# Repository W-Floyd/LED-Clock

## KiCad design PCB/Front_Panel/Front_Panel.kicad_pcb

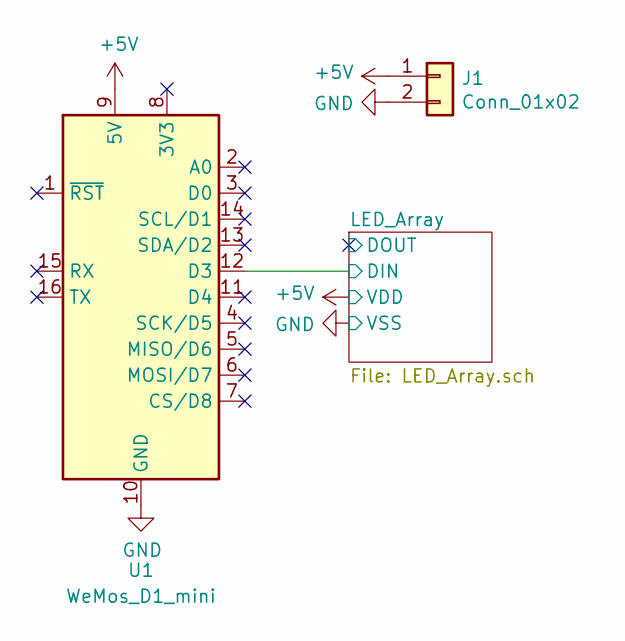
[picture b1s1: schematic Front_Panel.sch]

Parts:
J1: Conn_01x02; JST_XH_B2B-XH-AM_1x02_P2.50mm_Vertical
U1: WeMos_D1_mini; WEMOS_D1_mini_light

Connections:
+5V: J1.1, U1.9 (5V); also elsewhere on the board
/LED_Array/DIN: U1.12 (D3); also elsewhere on the board
GND: J1.2, U1.10 (GND); also elsewhere on the board

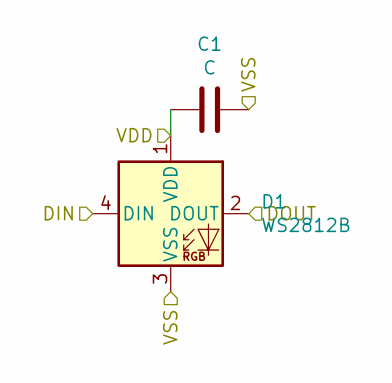
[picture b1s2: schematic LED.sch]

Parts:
C1: C; C_0402_1005Metric; LCSC Part C1525
D1: WS2812B; LED_WS2812B_PLCC4_5.0x5.0mm_P3.2mm; LCSC Part C114586

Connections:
+5V: C1.1, D1.1 (VDD); also elsewhere on the board
/LED_Array/Character/sheet607C81B4/DIN: D1.2 (DOUT); also elsewhere on the board
/LED_Array/DIN: D1.4 (DIN); also elsewhere on the board
GND: C1.2, D1.3 (VSS); also elsewhere on the board

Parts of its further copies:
C2, C3, C4, C5, C6, C7, C8, C9, C10, C11, C12, C13, C14, C15, C16, C17, C18, C19, C20, C21, C22, C23, C24, C25, C26, C27, C28: C; C_0402_1005Metric; LCSC Part C1525
D2, D3, D4, D5, D6, D7, D8, D9, D10, D11, D12, D13, D14, D15, D16, D17, D18, D19, D20, D21, D22, D23, D24, D25, D26, D27, D28: WS2812B; LED_WS2812B_PLCC4_5.0x5.0mm_P3.2mm; LCSC Part C114586

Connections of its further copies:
+5V: C2.1, C3.1, C4.1, C5.1, C6.1, C7.1, C8.1, C9.1, C10.1, C11.1, C12.1, C13.1, C14.1, C15.1, C16.1, C17.1, C18.1, C19.1, C20.1, C21.1, C22.1, C23.1, C24.1, C25.1, C26.1, C27.1, C28.1, D2.1 (VDD), D3.1 (VDD), D4.1 (VDD), D5.1 (VDD), D6.1 (VDD), D7.1 (VDD), D8.1 (VDD), D9.1 (VDD), D10.1 (VDD), D11.1 (VDD), D12.1 (VDD), D13.1 (VDD), D14.1 (VDD), D15.1 (VDD), D16.1 (VDD), D17.1 (VDD), D18.1 (VDD), D19.1 (VDD), D20.1 (VDD), D21.1 (VDD), D22.1 (VDD), D23.1 (VDD), D24.1 (VDD), D25.1 (VDD), D26.1 (VDD), D27.1 (VDD), D28.1 (VDD); also elsewhere on the board
/LED_Array/Character/sheet607C8FE9/DIN: D3.2 (DOUT), D4.4 (DIN)
/LED_Array/Character/sheet607C9E28/DIN: D5.2 (DOUT), D6.4 (DIN)
/LED_Array/Character/sheet607C81B4/DIN: D2.4 (DIN); also elsewhere on the board
/LED_Array/Character/sheet607C88E5/DIN: D2.2 (DOUT), D3.4 (DIN)
/LED_Array/Character/sheet607C96E8/DIN: D4.2 (DOUT), D5.4 (DIN)
/LED_Array/Character/sheet607CA522/DIN: D6.2 (DOUT), D7.4 (DIN)
/LED_Array/DOUT: D28.2 (DOUT)
/LED_Array/sheet607CAD2A/DIN: D7.2 (DOUT), D8.4 (DIN)
/LED_Array/sheet607CAD2A/sheet607C8FE9/DIN: D10.2 (DOUT), D11.4 (DIN)
/LED_Array/sheet607CAD2A/sheet607C9E28/DIN: D12.2 (DOUT), D13.4 (DIN)
/LED_Array/sheet607CAD2A/sheet607C81B4/DIN: D8.2 (DOUT), D9.4 (DIN)
/LED_Array/sheet607CAD2A/sheet607C88E5/DIN: D9.2 (DOUT), D10.4 (DIN)
/LED_Array/sheet607CAD2A/sheet607C96E8/DIN: D11.2 (DOUT), D12.4 (DIN)
/LED_Array/sheet607CAD2A/sheet607CA522/DIN: D13.2 (DOUT), D14.4 (DIN)
/LED_Array/sheet607CB27B/DIN: D14.2 (DOUT), D15.4 (DIN)
/LED_Array/sheet607CB27B/sheet607C8FE9/DIN: D17.2 (DOUT), D18.4 (DIN)
/LED_Array/sheet607CB27B/sheet607C9E28/DIN: D19.2 (DOUT), D20.4 (DIN)
/LED_Array/sheet607CB27B/sheet607C81B4/DIN: D15.2 (DOUT), D16.4 (DIN)
/LED_Array/sheet607CB27B/sheet607C88E5/DIN: D16.2 (DOUT), D17.4 (DIN)
/LED_Array/sheet607CB27B/sheet607C96E8/DIN: D18.2 (DOUT), D19.4 (DIN)
/LED_Array/sheet607CB27B/sheet607CA522/DIN: D20.2 (DOUT), D21.4 (DIN)
/LED_Array/sheet607CB803/DIN: D21.2 (DOUT), D22.4 (DIN)
/LED_Array/sheet607CB803/sheet607C8FE9/DIN: D24.2 (DOUT), D25.4 (DIN)
/LED_Array/sheet607CB803/sheet607C9E28/DIN: D26.2 (DOUT), D27.4 (DIN)
/LED_Array/sheet607CB803/sheet607C81B4/DIN: D22.2 (DOUT), D23.4 (DIN)
/LED_Array/sheet607CB803/sheet607C88E5/DIN: D23.2 (DOUT), D24.4 (DIN)
/LED_Array/sheet607CB803/sheet607C96E8/DIN: D25.2 (DOUT), D26.4 (DIN)
/LED_Array/sheet607CB803/sheet607CA522/DIN: D27.2 (DOUT), D28.4 (DIN)
GND: C2.2, C3.2, C4.2, C5.2, C6.2, C7.2, C8.2, C9.2, C10.2, C11.2, C12.2, C13.2, C14.2, C15.2, C16.2, C17.2, C18.2, C19.2, C20.2, C21.2, C22.2, C23.2, C24.2, C25.2, C26.2, C27.2, C28.2, D2.3 (VSS), D3.3 (VSS), D4.3 (VSS), D5.3 (VSS), D6.3 (VSS), D7.3 (VSS), D8.3 (VSS), D9.3 (VSS), D10.3 (VSS), D11.3 (VSS), D12.3 (VSS), D13.3 (VSS), D14.3 (VSS), D15.3 (VSS), D16.3 (VSS), D17.3 (VSS), D18.3 (VSS), D19.3 (VSS), D20.3 (VSS), D21.3 (VSS), D22.3 (VSS), D23.3 (VSS), D24.3 (VSS), D25.3 (VSS), D26.3 (VSS), D27.3 (VSS), D28.3 (VSS); also elsewhere on the board

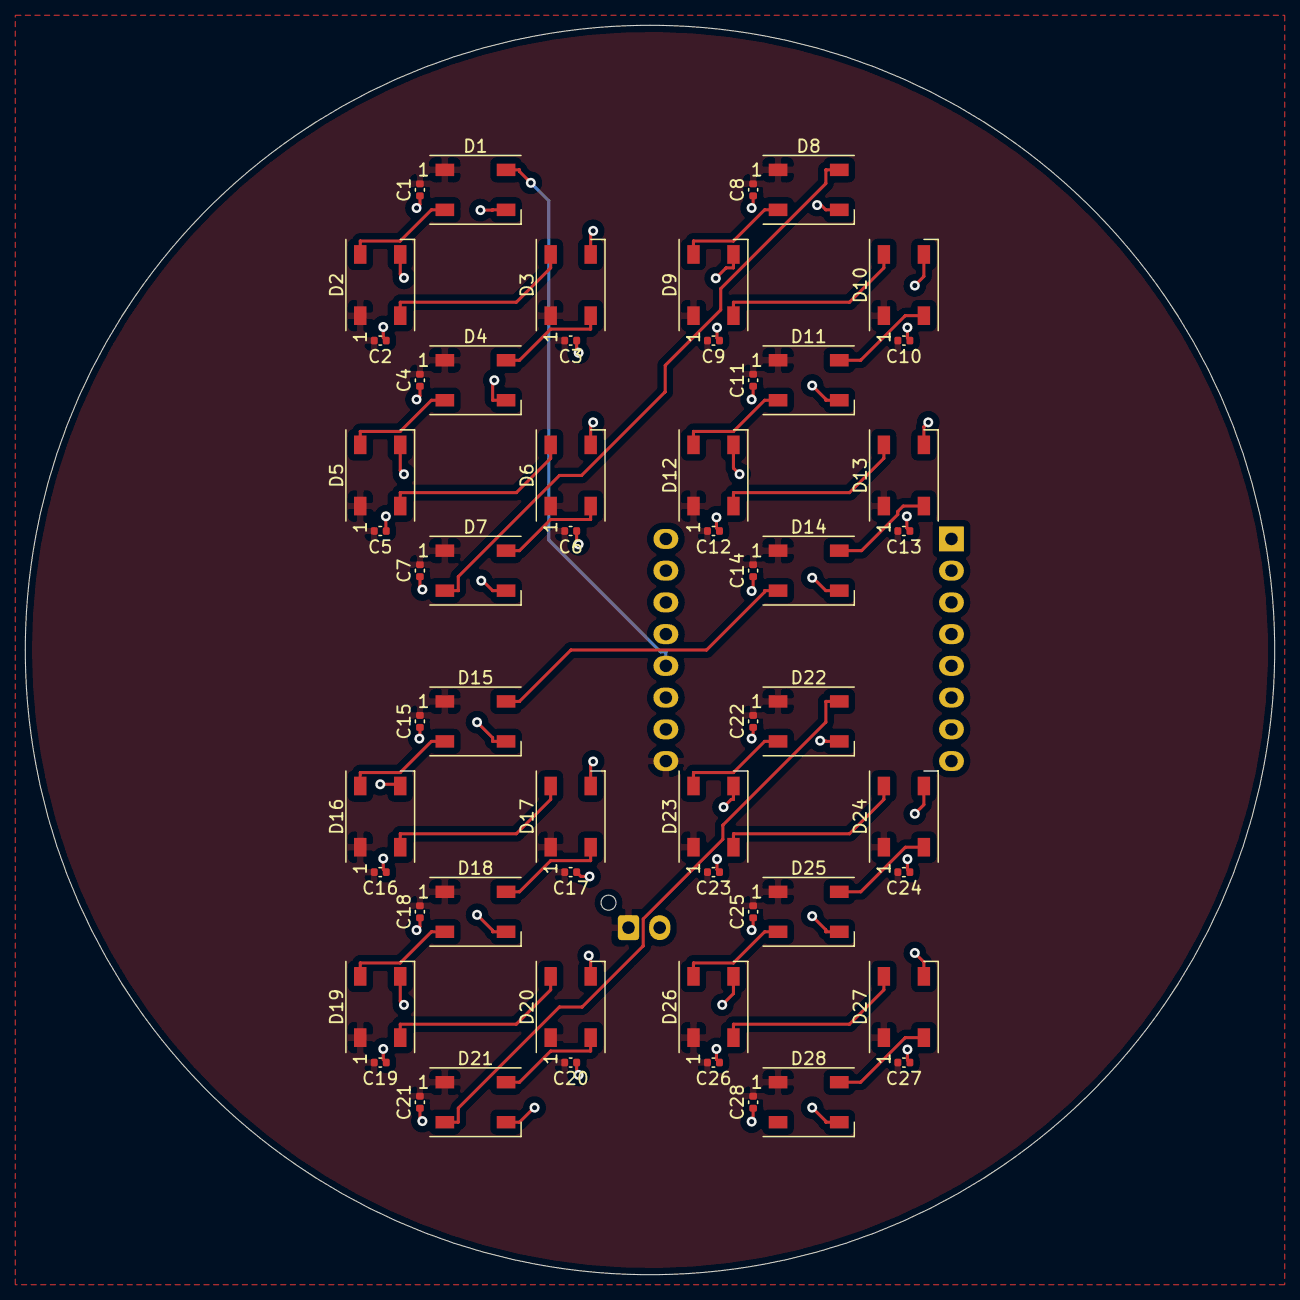
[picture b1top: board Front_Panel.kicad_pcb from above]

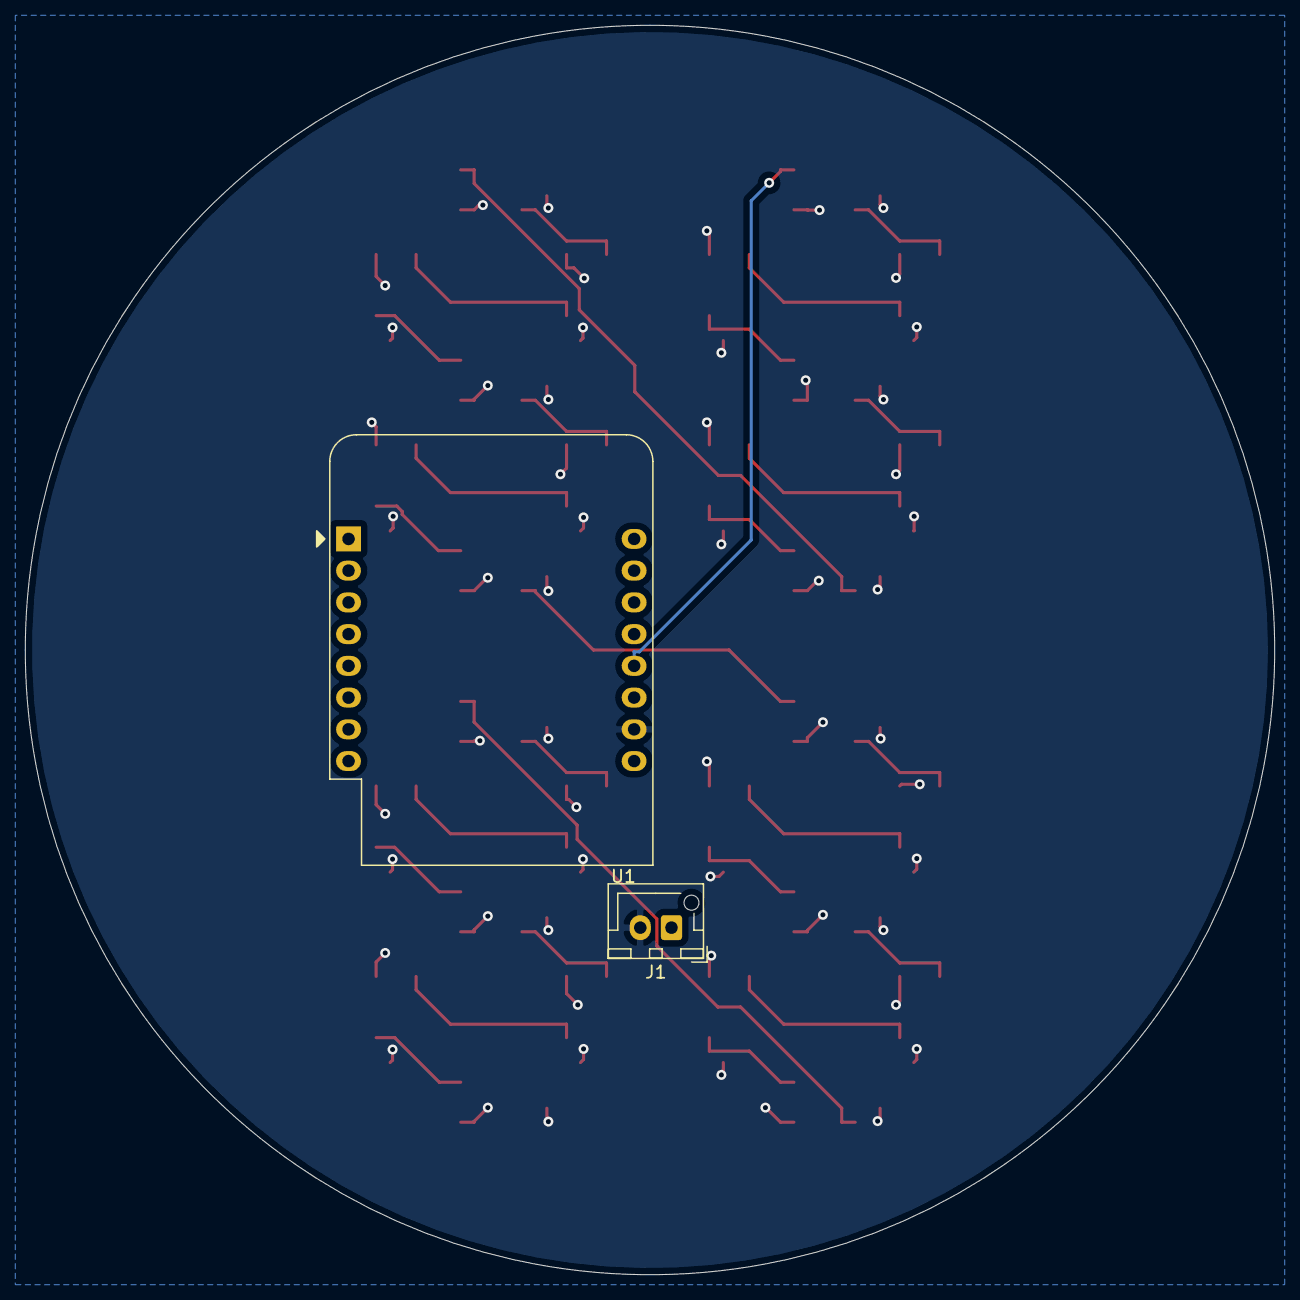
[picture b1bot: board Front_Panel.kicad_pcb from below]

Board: 2 copper layers, 100.0 x 100.0 mm, 58 parts (2 on the bottom side), 30 nets.

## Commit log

2021-03-22 all: Import.
2021-03-22 timezone: Add timezone setting.
2021-03-22 all: CRLF->LF
2021-04-19 PCB: Add clock PCB.
2021-05-03 all: Fix for PCB version, small changes.
